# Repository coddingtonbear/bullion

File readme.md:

# USB & SPI Interface for FS9721-based Multimeter (Bullion)

Do you have a cheap Chinese multimeter using the FS9721 chipset and
want to add an easy-to-use USB interface to it?  Or, do you have an
arduino project in mind where you might want to collect measurements
from your multimeter?  This project can help you do both of those things.

## Compatible Multimeters

Any multimeter using the FS9721 chipset is compatible, but you may have
to adapt the hardware design herein if your multimeter does not have a
3.5mm stereo jack labeled "RS232".

Known-compatible multimeters include:

* **RECOMMENDED** [TekPower TP4000ZC](https://www.amazon.com/Tekpower-TP4000ZC-Interfaced-Multimeter-Computer/dp/B000OPDFLM)
    * Also available as the Digitek DT-4000ZC.
    * Includes a 3.5mm RS232 port.
* [Mastech V&A 18B](https://www.amazon.com/Manual-Ranging-Digital-Multimeter-Interface/dp/B000LQONYM)
    * Does have an external RS232 port, but it is not compatible with the
      hardware files you'll find herein.  You will have to improvise.
* [UNI-T UT60E](https://www.amazon.com/UNI-T-UT60E-Precise-Light-Weight/dp/B0152OJAWC)
    * Does have an external RS232 port, but it is not compatible with the
      hardware files you'll find herein.  You will have to improvise.

## Interfaces

### USB

* Baud Rate: 2400

When connected to your PC, the device will appear as an additional serial
port (may require installation of a driver for the CH340G USB UART
chip).

By default, the raw output from the Multimeter will be displayed
as new multimeter data is received in a way identical to that of what the
built-in serial port would output were you to connect it directly to your
computer, but you can select a variety of output formats using the below
commands.

#### Commands

Commands are sent in the format `COMMAND=VALUE` followed by a single
newline character.

* Command ``output``:
    * Value ``raw`` (*default*): Display raw bytes received from multimeter.
    * Value ``value``: Display actual value scaled to base unit.
    * Value ``displayed``: Display displayed value.  Note that this is
      not scaled to the base unit.  Use the ``unit`` command below to
      determine magnitude.
    * Value ``none``: Disable output.
* Command ``units``:
    * Value ``0`` (*default*): Do not print unit.
    * Value ``1``: Print unit.  If the value is not scaled to the base
      unit, this may include an SI magnitude prefix ('u', 'n, 'm', 'k', 'M').

**Note**: *Command output is not displayed until you press <ENTER>*

For example; to display units in the format they are displayed on the screen,
you could send the following two commands:

```
output=displayed
units=1
```

and you would, assuming you were measuring a voltage source, receive responses like:

```
1.244 mV
1.239 mV
```

But, if you wanted to output values scaled to their base unit so programs
consuming these values wouldn't need to worry about the SI magnitude, you
could instead send the following commands:

```
output=value
units=1
```

and you'd receive the following values:

```
0.001244 V
0.001239 V
```

You could even turn off unit display if you were not concerned about
identifying what mode the multimeter was in while the returned measurement
was taking place (note, though, that `units=0` is the default state, so
you need not send that command if you have not already enabled unit display):

```
output=value
units=0
```

and then you'd receive very easy-to-parse values:

```
0.001244
0.001239
```

### SPI

Every SPI transaction is a single 8-bit command ID, followed by a
32-bit response.

The following commands are implemented:

* `0x01`: Return multimeter measurement as IEEE 754 floating point value; this
  value is scaled to the appropriate base unit for the mode in which the
  multimeter is currently operating..
* `0x02`: Return multimeter display as IEEE 754 floating point value.
  Note that this value is not scaled to handle displayed SI magnitudes!
* `0x10`: Return current display flags as bits in this order:
  * 31:
  * 30: Sign
  * 29: Low Battery
  * 28: Hold
  * 27: Rel
  * 26: Beep
  * 25: Sign (?)
  * **24**: RS232
  * 23: AUTO
  * 22: 
  * 21: 
  * 20: M (mega)
  * 19: k (kilo)
  * 18: m (milli)
  * 17: n (nano)
  * **16**: µ (micro)
  * 15: C2C1 00 (?)
  * 14: C2C1 01 (?)
  * 13: C2C1 10 (?)
  * 12: C2C1 11 (?)
  * 11:
  * 10: Diode
  * 09: DC
  * **08**: AC
  * 07:
  * 06:
  * 05: %
  * 04: Hz
  * 03: V
  * 02: A
  * 01: F
  * 00: Ω

#### SPI Troubleshooting

The device itself operates as an SPI slave, and it's rather difficult to
keep up with fast SPI speeds with just a 12Mhz clock, so if you have unreliable
results, try slowing down your SPI bus speed -- it's not like you're
going to ever be able to get more than a few measurements/second
anyway given that the multimeter itself only measures 2-3x second.

#### Arduino Example

```c
#include <SPI.h>

#define MM_PIN 9

void setup() {
  digitalWrite(MM_PIN, HIGH);
  pinMode(MM_PIN, OUTPUT);
  pinMode(MISO, INPUT);
  pinMode(MOSI, OUTPUT);
  pinMode(SCK, OUTPUT);
  SPI.begin();
  SPI.beginTransaction(SPISettings(1000, MSBFIRST, SPI_MODE0));

  Serial.begin(9600);
}

void loop() {
  union {
      float measurement;
      unsigned char bytes[4];
  } floatMeasurement;

  digitalWrite(MM_PIN, LOW);

  // Let's get the current measurement
  SPI.transfer(0x01);
  for(uint8_t i = 0; i < 4; i++) {
    floatMeasurement.bytes[i] = SPI.transfer(i);
  }
  Serial.println(floatMeasurement.measurement, 7);
  digitalWrite(MM_PIN, HIGH);

  delay(500);

  // Now let's print the current flags
  digitalWrite(MM_PIN, LOW);
  SPI.transfer(0x10);
  for(uint8_t i = 0; i < 4; i++) {
    Serial.println(SPI.transfer(i), BIN);
  }
  digitalWrite(MM_PIN, HIGH);

  delay(3000);
}
```

## Hardware

Check out the `hardware` directory to find Kicad schematics and layout.  The
layout you'll find was designed for *homemade* *pcb* *fabrication* (note how 
big the vias are and the presence of "transit" vias for working around the
lack of through-hole plating), but it could be sent to your favorite PCB
boardhouse for manufacture if desired.

The following major components are used (see the schematic for details):

* ATMEGA328PB Microcontroller in the QFP package. A normal ATMEGA328P
  would work fine, too, but you will have to update a handful of SPI-related
  register and interrupt names to remove the extra zero (the -PB version
  has two SPI peripherals).
  Although the ATMEGA328PB is a little more capable than the ATMEGA328P
  these days, they are just a little cheaper; both are around 2.5 USD.
* CH340G USB-to-UART IC: You can buy these from Aliexpress or wherever
  for less than 0.50 USD.
* 12Mhz Crystal (SMD HC-49)
* A MicroUSB connector.
* A standard through-hole 3.5mm stereo connector.

Note that the design relies upon the CH340G chip sharing the
microcontroller's clock; you will want to set the `CKOUT=0` fuse
(generally titled "Clock output on PORTB0").

## Future Thoughts

There are lots of things about this project that I'd change if I were to
approach it again; those include:

* Making the primary serial interface I2C instead of SPI.
    * I2C provides a lot more flexibility for letting a device take
      extra time to perform slow operations via "clock stretching".  As
      this is currently designed, SPI is used, and the client device must
      be able to keep up with the clock speed set by the master or data
      will be lost.
    * With I2C, you can save a wire or two!
    * The downside is that we might have to expose a couple extra pins
      since the current header is used for both programming and the serial
      interface.  If I2C is added, either two additional header pins will
      need to be added, or maybe a multiplexer chip allowing two header
      pins to be shared individually between two different microcontroller
      pins.
* Orient the microcontroller at a 45˚ angle.  This should make routing a
  little less chaotic.
* Add reverse current protection!  Not having such protection was a little
  bit of an embarassing oversight.
* Use either a MicroUSB breakout board or a MiniUSB connector instead of
  the existing MicroUSB connector. Soldering that tiny connector onto
  a homemade PCB is very difficult -- the pin pitch of those connectors
  is 0.65mm; just a smidge below what my current process is able to
  resolve (~0.75mm) without needing to use a sharp knife to separate
  traces.
* Perhaps place devices on both sides of the board to save space?  It's
  not clear to me whether that would be worth it, but it could make the
  board a lot smaller.

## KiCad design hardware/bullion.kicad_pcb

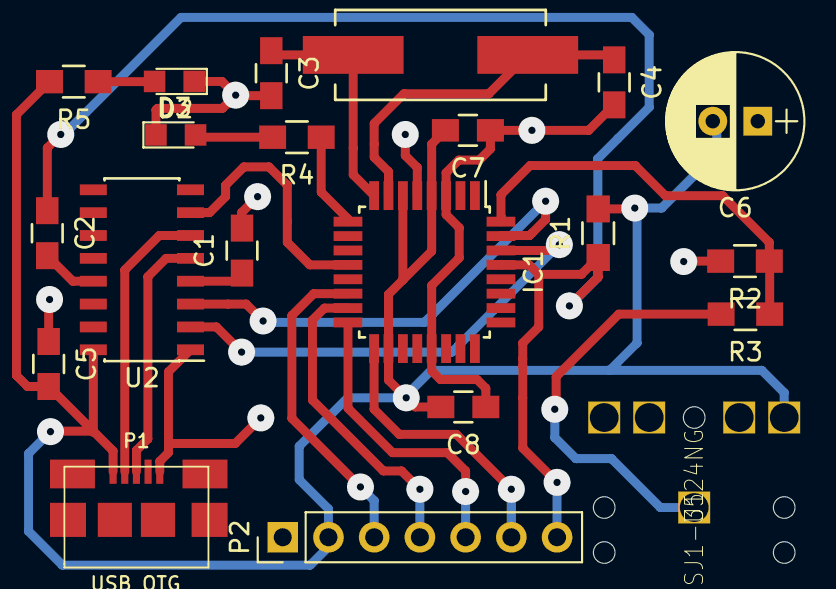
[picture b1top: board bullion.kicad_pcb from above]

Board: 2 copper layers, 21 parts (0 on the bottom side), 21 nets.

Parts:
C1, C2, C5, C7, C8: 0.1u; C_0805_HandSoldering
C3, C4: 22p; C_0805_HandSoldering
C6: 47u; CP_Radial_D7.5mm_P2.50mm
D2: BLUE; LED_0805
D3: RED; LED_0805
IC1: ATMEGA328P-A; TQFP-32_7x7mm_Pitch0.8mm
P1: USB_OTG; MICRO-B_USB
P2: CONN_01X07; Pin_Header_Straight_1x07_Pitch2.54mm
R1: 10k; R_0805_HandSoldering
R2: 2.2k; R_0805_HandSoldering
R3, R5: 220; R_0805_HandSoldering
R4: 82; R_0805_HandSoldering
U1: SJ1-3524NG; PIN-4
U2: CH340G; SOIC-16_3.9x9.9mm_Pitch1.27mm
Y1: Crystal; Crystal_HC49-SD_SMD

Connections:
+5V: C5.2, C6.2, C7.2, C8.2, IC1.4, IC1.6, IC1.18, P1.1, P2.2, R1.2, R5.2, U1.2, U2.16
CLKOUT: IC1.12, U2.7
DTR: C2.2, U2.13
GND: C1.2, C3.2, C4.2, C5.1, C6.1, C7.1, C8.1, D2.1, D3.1, IC1.3, IC1.5, IC1.21, P1.5, P2.1, R2.2, U2.1
MM_TXD: IC1.32, R2.1, R3.1
unnamed: C1.1, U2.4
unnamed: C2.1, IC1.29, P2.7, R1.1
unnamed: C3.1, IC1.8, Y1.1
unnamed: C4.1, IC1.7, Y1.2
unnamed: D2.2, R4.2
unnamed: D3.2, R5.1
unnamed: IC1.9, R4.1
unnamed: IC1.14, P2.3
unnamed: IC1.15, P2.4
unnamed: IC1.16, P2.5
unnamed: IC1.17, P2.6
unnamed: P1.2, U2.6
unnamed: P1.3, U2.5
unnamed: R3.2, U1.1
RXD: IC1.30, U2.2
TXD: IC1.31, U2.3

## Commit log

2017-01-16 And so it begins...
2017-01-21 Adding LEDs; fixing RS232 connection.
2017-01-22 Updating hardware to latest revision; adding readme.
2017-01-22 Minor typo.
2017-01-22 Polishing-up readme for bullion.
2017-01-22 Adding board rendering.
2017-01-22 Fixing board layout image.
2017-01-22 Let's just use a direct link.
2017-01-22 Serve via rawgit.
2017-01-22 Fixing typo.
2017-01-22 Another typo.
2017-01-23 Adding image of the fully-connected setup.
2017-01-23 Adding 'Future Thoughts' section.
2017-02-06 Adding project name to title.
2017-02-07 Renaming 'software' to 'firmware' for accuracy.
2017-02-20 Adding schematic.
2017-02-20 Removing SVG plot of hardware.
